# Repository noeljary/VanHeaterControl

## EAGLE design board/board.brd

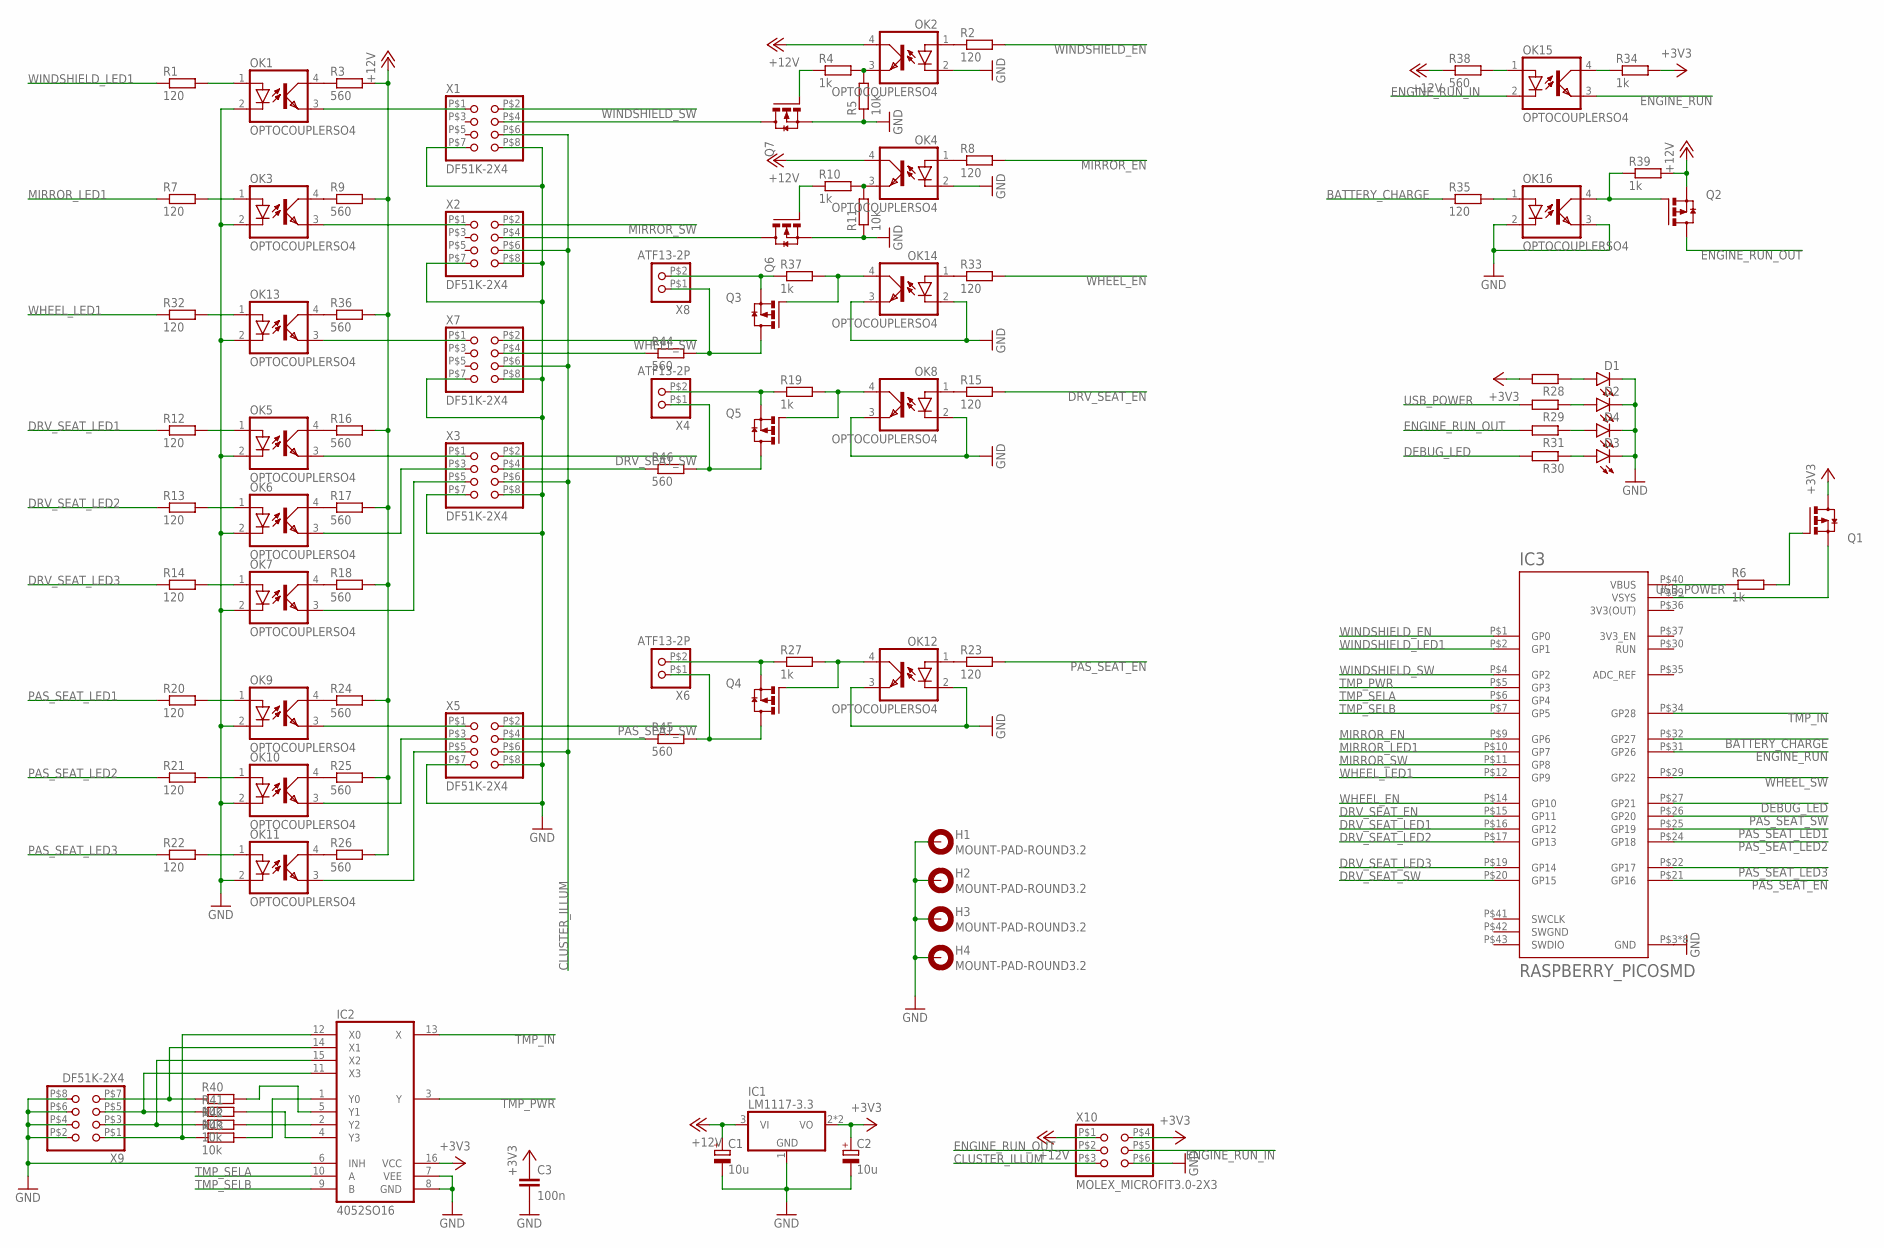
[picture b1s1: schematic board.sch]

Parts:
C1, C2: 10u; C_4MM
C3: 100n; C0805
D1, D2, D3, D4: LED1206; CHIPLED_1206
H1, H2, H3, H4: MOUNT-PAD-ROUND3.2; 3,2-PAD
IC1: LM1117-3.3; SOT223
IC2: 4052SO16; SO16
IC3: RASPBERRY_PICOSMD; PICO-PKG-SMD
OK1, OK2, OK3, OK4, OK5, OK6, OK7, OK8, OK9, OK10, OK11, OK12, OK13, OK14, OK15, OK16: OPTOCOUPLERSO4; SO04
Q1, Q2: MOSFET_P_CHANNELSOT23; SOT23
Q3, Q4, Q5: MOSFET_P_CHANNELTO252; TO252
Q6, Q7: MOSFET_N_CHANNELSOT23; SOT23
R1, R2, R7, R8, R12, R13, R14, R15, R20, R21, R22, R23, R32, R33, R35: 120; R0805
R3, R9, R16, R17, R18, R24, R25, R26, R36, R38, R44, R45, R46: 560; R0805
R4, R6, R10, R19, R27, R34, R37, R39: 1k; R0805
R5, R11, R40, R41, R42, R43: 10k; R0805
R28, R29, R30, R31: RESISTOR0805; R0805
X1, X2, X3, X5, X7, X9: DF51K-2X4
X4, X6, X8: ATF13-2P
X10: MOLEX_MICROFIT3.0-2X3

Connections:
3V3(OUT): IC3.P$36 (3V3(OUT))
+3V3: C2.+, C3.1, IC1.2 (VO), IC1.4 (VO), IC2.16 (VCC), Q1.3 (D), R28.2, R34.2, X10.P$4 (2)
+12V: C1.+, IC1.3 (VI), OK2.4 (COL), OK4.4 (COL), Q2.2 (S), R3.2, R9.2, R16.2, R17.2, R18.2, R24.2, R25.2, R26.2, R36.2, R38.1, R39.2, X10.P$1 (1)
BATTERY_CHARGE: IC3.P$32 (GP27), R35.1
CLUSTER_ILLUM: X1.P$6 (6), X2.P$6 (6), X3.P$6 (6), X5.P$6 (6), X7.P$6 (6), X10.P$3 (5)
DEBUG_LED: IC3.P$27 (GP21), R30.2
DRV_SEAT_EN: IC3.P$15 (GP11), R15.2
DRV_SEAT_LED1: IC3.P$16 (GP12), R12.1
DRV_SEAT_LED2: IC3.P$17 (GP13), R13.1
DRV_SEAT_LED3: IC3.P$19 (GP14), R14.1
DRV_SEAT_SW: IC3.P$20 (GP15), X3.P$2 (2)
ENGINE_RUN: IC3.P$31 (GP26), OK15.3 (EMIT)
ENGINE_RUN_IN: OK15.2 (C), X10.P$5 (4)
ENGINE_RUN_OUT: Q2.3 (D), R31.2, X10.P$2 (3)
GND: C1.-, C2.-, C3.2, D1.C, D2.C, D3.C, D4.C, H1.B3,2, H1.P$1, H1.P$2, H1.P$3, H1.P$4, H1.P$5, H1.P$6, H1.P$7, H1.P$8, H2.B3,2, H2.P$1, H2.P$2, H2.P$3, H2.P$4, H2.P$5, H2.P$6, H2.P$7, H2.P$8, H3.B3,2, H3.P$1, H3.P$2, H3.P$3, H3.P$4, H3.P$5, H3.P$6, H3.P$7, H3.P$8, H4.B3,2, H4.P$1, H4.P$2, H4.P$3, H4.P$4, H4.P$5, H4.P$6, H4.P$7, H4.P$8, IC1.1 (GND), IC2.6 (INH), IC2.7 (VEE), IC2.8 (GND), IC3.P$3 (GND), IC3.P$8 (GND), IC3.P$13 (GND), IC3.P$18 (GND), IC3.P$23 (GND), IC3.P$28 (GND), IC3.P$33 (GND), IC3.P$38 (GND), OK1.2 (C), OK2.2 (C), OK3.2 (C), OK4.2 (C), OK5.2 (C), OK6.2 (C), OK7.2 (C), OK8.2 (C), OK8.3 (EMIT), OK9.2 (C), OK10.2 (C), OK11.2 (C), OK12.2 (C), OK12.3 (EMIT), OK13.2 (C), OK14.2 (C), OK14.3 (EMIT), OK16.2 (C), OK16.3 (EMIT), Q6.2 (S), Q7.2 (S), R5.1, R11.1, X1.P$7 (7), X1.P$8 (8), X2.P$7 (7), X2.P$8 (8), X3.P$7 (7), X3.P$8 (8), X5.P$7 (7), X5.P$8 (8), X7.P$7 (7), X7.P$8 (8), X9.P$2 (2), X9.P$4 (4), X9.P$6 (6), X9.P$8 (8), X10.P$6 (6)
MIRROR_EN: IC3.P$9 (GP6), R8.2
MIRROR_LED1: IC3.P$10 (GP7), R7.1
MIRROR_SW: IC3.P$11 (GP8), X2.P$2 (2)
unnamed: OK1.3 (EMIT), X1.P$1 (1)
unnamed: OK1.4 (COL), R3.1
unnamed: OK3.4 (COL), R9.1
unnamed: OK13.4 (COL), R36.1
unnamed: IC2.1 (Y0), R43.2
unnamed: IC2.2 (Y2), R42.2
unnamed: OK5.4 (COL), R16.1
unnamed: OK6.4 (COL), R17.1
unnamed: OK7.4 (COL), R18.1
unnamed: OK9.4 (COL), R24.1
unnamed: OK10.4 (COL), R25.1
unnamed: OK11.4 (COL), R26.1
unnamed: OK3.3 (EMIT), X2.P$1 (1)
unnamed: OK13.3 (EMIT), X7.P$1 (1)
unnamed: IC2.4 (Y3), R41.2
unnamed: IC2.5 (Y1), R40.2
unnamed: OK9.3 (EMIT), X5.P$1 (1)
unnamed: OK5.3 (EMIT), X3.P$1 (1)
unnamed: OK6.3 (EMIT), X3.P$3 (3)
unnamed: OK7.3 (EMIT), X3.P$5 (5)
unnamed: OK10.3 (EMIT), X5.P$3 (3)
unnamed: OK11.3 (EMIT), X5.P$5 (5)
unnamed: OK1.1 (A), R1.2
unnamed: OK3.1 (A), R7.2
unnamed: OK13.1 (A), R32.2
unnamed: D1.A, R28.1
unnamed: OK5.1 (A), R12.2
unnamed: OK6.1 (A), R13.2
unnamed: OK7.1 (A), R14.2
unnamed: OK9.1 (A), R20.2
unnamed: OK10.1 (A), R21.2
unnamed: OK11.1 (A), R22.2
unnamed: IC2.14 (X1), R40.1, X9.P$7 (7)
unnamed: OK2.1 (A), R2.1
unnamed: OK2.3 (EMIT), R4.2, R5.2
unnamed: Q7.3 (D), X1.P$4 (4)
unnamed: Q7.1 (G), R4.1
unnamed: Q6.3 (D), X2.P$4 (4)
unnamed: OK4.3 (EMIT), R10.2, R11.2
unnamed: OK4.1 (A), R8.1
unnamed: Q6.1 (G), R10.1
unnamed: OK14.1 (A), R33.1
unnamed: Q3.2 (S), R37.1, X8.P$2 (2)
unnamed: OK14.4 (COL), Q3.1 (G), R37.2
unnamed: Q3.3 (D), R44.2, X8.P$1 (1)
unnamed: R44.1, X7.P$4 (4)
unnamed: R46.1, X3.P$4 (4)
unnamed: Q5.3 (D), R46.2, X4.P$1 (1)
unnamed: OK8.1 (A), R15.1
unnamed: Q5.2 (S), R19.1, X4.P$2 (2)
unnamed: OK8.4 (COL), Q5.1 (G), R19.2
unnamed: R45.1, X5.P$4 (4)
unnamed: Q4.3 (D), R45.2, X6.P$1 (1)
unnamed: OK15.1 (A), R38.2
unnamed: Q4.2 (S), R27.1, X6.P$2 (2)
unnamed: OK12.1 (A), R23.1
unnamed: OK12.4 (COL), Q4.1 (G), R27.2
unnamed: OK15.4 (COL), R34.1
unnamed: OK16.1 (A), R35.2
unnamed: OK16.4 (COL), Q2.1 (G), R39.1
unnamed: IC2.11 (X3), R41.1, X9.P$5 (5)
unnamed: Q1.1 (G), R6.2
unnamed: IC3.P$39 (VSYS), Q1.2 (S)
unnamed: D2.A, R29.1
unnamed: D4.A, R31.1
unnamed: D3.A, R30.1
unnamed: IC2.15 (X2), R42.1, X9.P$3 (3)
unnamed: IC2.12 (X0), R43.1, X9.P$1 (1)
PAS_SEAT_EN: IC3.P$21 (GP16), R23.2
PAS_SEAT_LED1: IC3.P$25 (GP19), R20.1
PAS_SEAT_LED2: IC3.P$24 (GP18), R21.1
PAS_SEAT_LED3: IC3.P$22 (GP17), R22.1
PAS_SEAT_SW: IC3.P$26 (GP20), X5.P$2 (2)
SWGND: IC3.P$42 (SWGND)
TMP_IN: IC2.13 (X), IC3.P$34 (GP28)
TMP_PWR: IC2.3 (Y), IC3.P$5 (GP3)
TMP_SELA: IC2.10 (A), IC3.P$6 (GP4)
TMP_SELB: IC2.9 (B), IC3.P$7 (GP5)
USB_POWER: IC3.P$40 (VBUS), R6.1, R29.2
WHEEL_EN: IC3.P$14 (GP10), R33.2
WHEEL_LED1: IC3.P$12 (GP9), R32.1
WHEEL_SW: IC3.P$29 (GP22), X7.P$2 (2)
WINDSHIELD_EN: IC3.P$1 (GP0), R2.2
WINDSHIELD_LED1: IC3.P$2 (GP1), R1.1
WINDSHIELD_SW: IC3.P$4 (GP2), X1.P$2 (2)

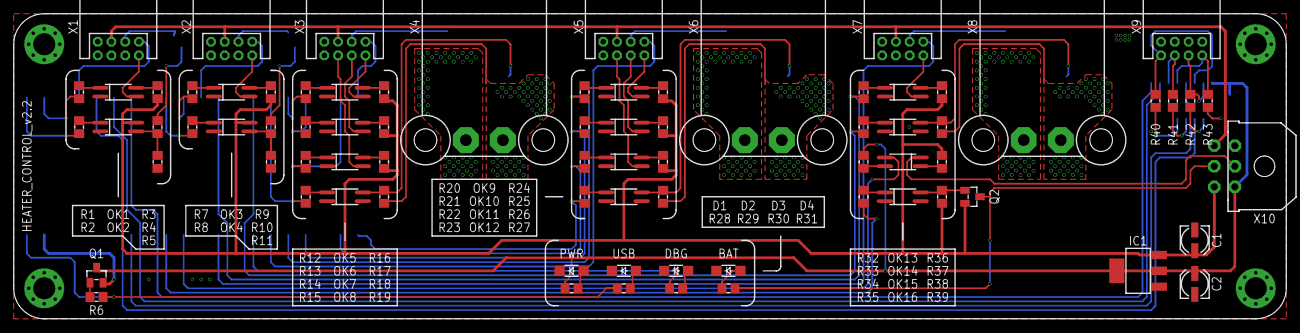
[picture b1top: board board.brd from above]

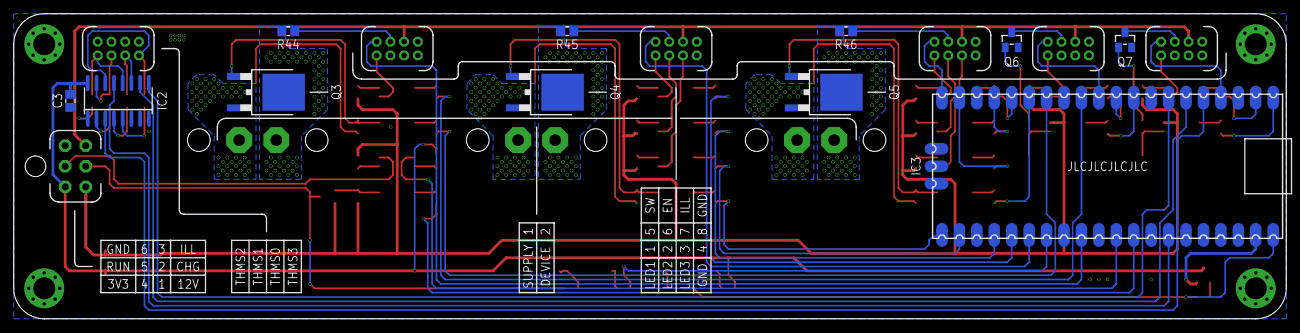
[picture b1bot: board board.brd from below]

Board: 2 copper layers, 185.4 x 44.5 mm, 93 parts (11 on the bottom side), 101 nets.

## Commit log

2022-11-26 Add Van Heater Control to Git
2023-03-30 Version 2.1 board with corrected Pi Power MOSFET and Temperature Connections
2023-03-30 Updated code reflecting defect fixes and board layout change.
2023-03-30 Updated board layout with pulldown resistors for N channel MOSFETS
